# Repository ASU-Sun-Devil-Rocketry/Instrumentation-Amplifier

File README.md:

<h1>Rail to Rail Instrumentation Amplifier with Regulated Supply</h1>

<p><u>Current PCB Revision:</u> 2.0 <p>
<p>PCB Part Number: L0001</p>
<p>Design Folder: <a href="https://drive.google.com/drive/folders/1LhDJDFwJdzdXdzs4db-Y9qnFIhuEQvka">Click Here</a></p>

<p>The instrumentation amplifier IC uses an adjustable gain differential amplifier with buffered inputs to amplify the readings from an analog sensor using a wheatstone bridge such as a load cell or pressure transducer. The amplifier supply voltage was chosen to match that of the pressure transducers it is intended to be used with.</p>

<b>Working Directory Structure:</b>

<p>
   doc: documentation
   
   src: source design files, e.g. schematic and board files

   lib: libraries for schematic symbols and footprints

   production: files needed for pcb fabrication, e.g. gerbers, profile, drill file

   sim: simulation files 

   cad: 3d models
  
   img: images of circuit/footprints for github display 
</p>

<h2>Schematic:</h2>

<h2>PCB Layout: </h2>

<h2>Gerber Veiws:</h2>

<h2> 3D Model: </h2>

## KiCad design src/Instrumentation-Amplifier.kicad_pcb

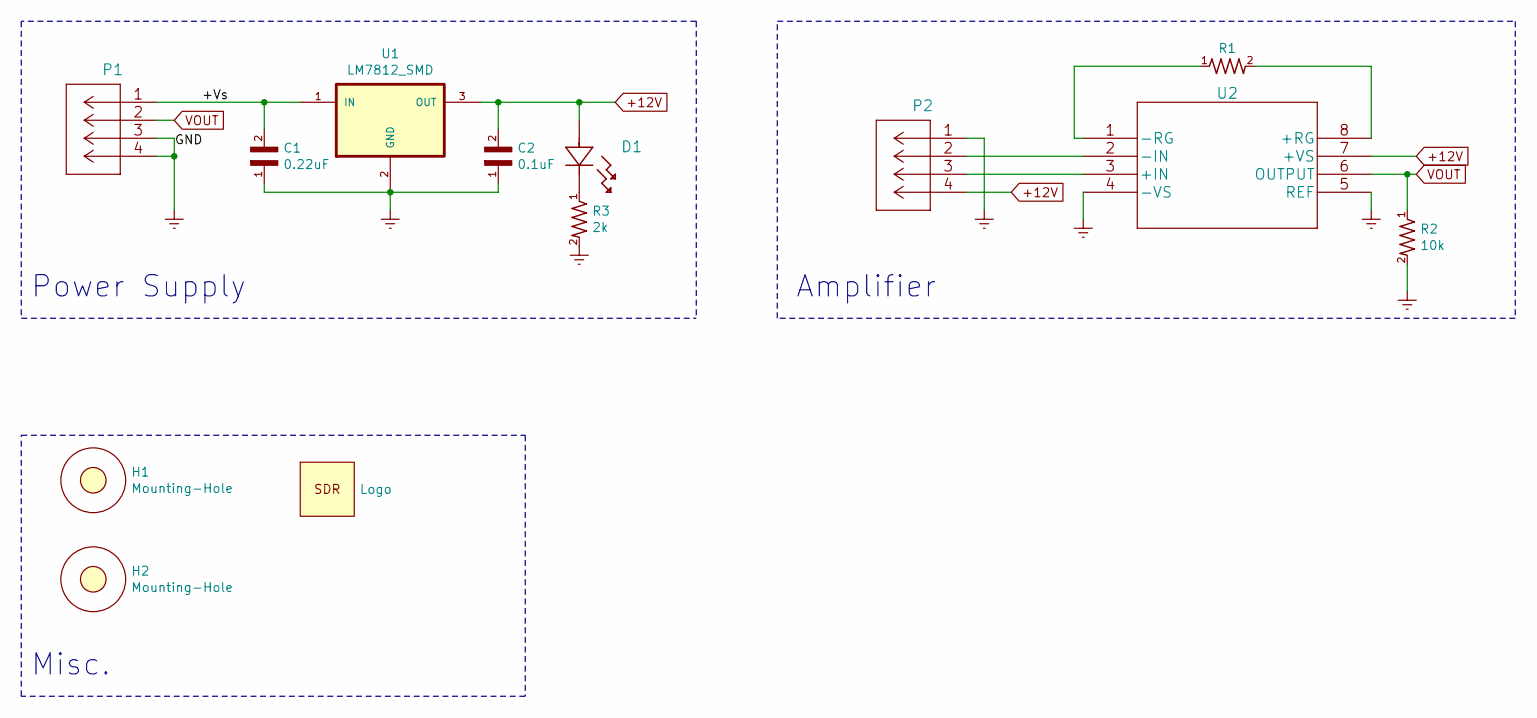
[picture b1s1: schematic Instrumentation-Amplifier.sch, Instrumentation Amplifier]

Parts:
C1: 0.22uF; CAP_0603
C2: 0.1uF; CAP_0603
D1: LTST-C150GKT
H1, H2: Mounting-Hole; MountingHole_2.1mm
LOGO1: Logo; logo2
P1, P2: 2043-1X04G00DAU
R1: RG; RES_0603
R2: 10k; RES_0603
R3: 2k; RES_0603
U1: LM7812_SMD; LM7812; PARTREV 34
U2: AD623ARZ-R7

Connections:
+12V: C2.2, D1.2, P2.4, U1.3 (OUT), U2.7 (+VS)
/+Vs: C1.2, P1.1, U1.1 (IN)
Earth: C1.1, C2.1, P1.3, P1.4, P2.1, R2.2, R3.2, U1.2 (GND), U2.4 (-VS), U2.5 (REF)
unnamed: D1.1, R3.1
unnamed: P2.2, U2.2 (-IN)
unnamed: P2.3, U2.3 (+IN)
unnamed: R1.1, U2.1 (-RG)
unnamed: R1.2, U2.8 (+RG)
VOUT: P1.2, R2.1, U2.6 (OUTPUT)

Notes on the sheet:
Power Supply
Amplifier
Misc.

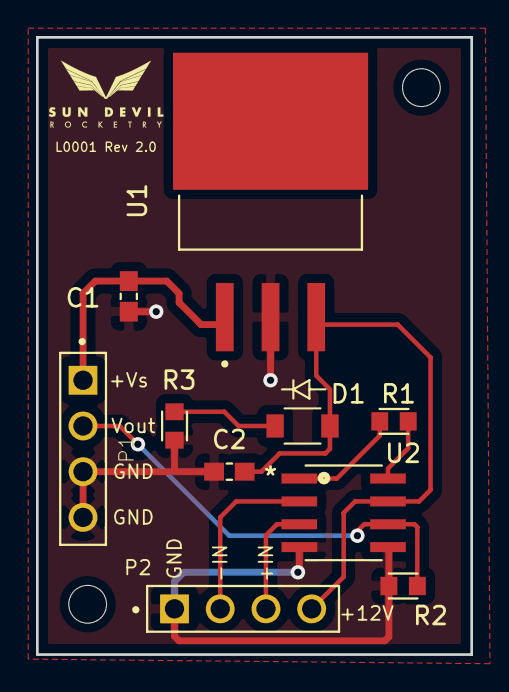
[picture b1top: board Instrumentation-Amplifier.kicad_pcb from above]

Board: 2 copper layers, 24.1 x 34.3 mm, 13 parts (0 on the bottom side), 9 nets.

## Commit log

2021-06-05 Added directory structure description to readme
2021-06-05 indent readme
2021-06-05 Undo indent readme
2021-06-05 Copied files from old repo
2021-06-05 Added readme
2021-06-05 Added readmes
2021-06-05 Updated PCB Revision Number
2021-06-05 Underlined Revision
2021-06-06 Updated part number
2021-06-12 Revision 2 uploaded
2021-06-13 Created first revision of rev 2 BOM
2021-06-13 Added 3d files for parts on BOM
2021-06-13 removed file
2021-06-13 Updated CAD folder README description
2021-06-13 Generated Rev 2.0 Gerbers
2021-06-13 Added gerberView images
2021-06-13 Added labels to README images
2021-06-13 Generated Step file
2021-06-13 Fixed Incorrect img filename
2021-06-13 Cleaned up file structure
2021-06-18 Added init method
2021-06-19 removed pycache
2021-06-19 Converted user inputs to floating point
2021-06-19 Push test
2021-06-20 Added functions to check if amplfication method and dof are valid entries
2021-06-20 Added enterInputs function
2021-06-20 Added method to calculate target gain and offset
2021-06-20 Started method for resistor calculations
2021-06-20 Added function for calculating gain resistor
2021-06-26 Modified 3D cap fit on footprint
2021-06-30 Re-added power library
2021-09-07 Added design folder link to README
2021-09-23 Fixed issue with decoupling cap placement
2021-09-28 Added earth symbol to component lib
2021-09-28 Swapped 4 pin header component symbol
2021-09-28 Updated schematic with global labels
2021-09-28 Updated PCB with new connectors
2021-09-28 Added mounting holes
2021-10-02 Added LED resistor
2022-03-02 Added new 3D view image
2022-03-02 renamed 3D view image
2022-03-02 fixed 3D veiw image file extension
2022-06-26 minor local edits

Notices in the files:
parts and their libraries:
Copyright 2021 Accelerated Designs. All rights reserved.
